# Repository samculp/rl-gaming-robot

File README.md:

# RL Gaming Robot

The RL Gaming Robot is a senior design project focused on developing a Reinforcement Learning system that learns to play games through repeated attempts and applies its learned behavior to a game to ultimately improve its score.

The current target game is Tetris. The long-term goal is for the RL agent to make gameplay decisions and output controller commands that are translated into physical actions pressed on a controller by a robotic system.

This repository contains the software and hardware elements used to create the project.

## Repository Structure

```text
RL-Gaming-Robot/

├── hardware/
│   ├── experiments/
│   │   ├── actuator_pulse/
│   │   └── cad_files/
│   └── production/
│
├── software/
│   ├── requirements/
│   ├── environment/
│   ├── agent/
│   └── test_cases/
│
└── README.md
```

## Hardware

The `hardware` directory contains the mechanical and electronic development files for the RL Gaming Robot.

This includes:

* Actuator experiments and testing
* CAD models and mechanical designs
* Controller mounting and interaction components
* Production hardware designs
* Hardware documentation and validation

See the [hardware README](hardware/README.md) for additional information.

## Software

The `software` directory contains the software required to develop and operate the RL system.

This includes:

* Python environment and dependency requirements
* Game environment code
* Reinforcement Learning agent code
* Software test cases

The software is responsible for interacting with the game environment, training and executing the RL agent, and producing controller actions for the hardware system.

See the [software README](software/README.md) for additional information.

## System Overview

The intended system operates as a feedback loop:

```text
┌─────────────────┐
│    NES Tetris   │
└────────┬────────┘
         │
         │ Game State
         ▼
┌─────────────────┐
│ Game Environment│
└────────┬────────┘
         │
         │ State
         ▼
┌─────────────────┐
│    RL Agent     │
└────────┬────────┘
         │
         │ Controller Action
         ▼
┌─────────────────┐
│ Robot Controller│
└────────┬────────┘
         │
         │ Physical Command
         ▼
┌─────────────────┐
│  Robotic System  │
└────────┬────────┘
         │
         │ Button Press
         ▼
┌─────────────────┐
│  NES Controller │
└────────┬────────┘
         │
         └──────────────► NES Tetris
```

The game produces a new state after each action, allowing the RL agent to continually evaluate the game and select its next action.

## Testing

Testing is an integral part of the project and is performed throughout both software and hardware development.

Software testing focuses on:

* Game-state processing
* RL agent behavior
* Action generation
* Software component integration
* Model performance and repeatability

Hardware testing focuses on:

* Actuator performance
* Button press accuracy
* Timing and reliability
* Mechanical positioning
* Hardware/software integration

Test cases are maintained within the appropriate software and hardware directories.

## Development Philosophy

The project is organized around **experimentation, validation, and integration**.

Development follows these general principles:

1. **Experiment** — Develop and test individual concepts and components.
2. **Validate** — Verify that components meet their intended requirements.
3. **Integrate** — Combine validated software and hardware components.
4. **Test** — Evaluate the complete system and identify integration issues.
5. **Iterate** — Use test results to improve the system.

Experimental implementations should be validated before being incorporated into the production system.

## Project Goals

The primary goals of the RL Gaming Robot project are to:

* Develop an RL agent capable of improving its gameplay through repeated attempts.
* Create a software environment for training and evaluating the agent.
* Develop a robotic system capable of physically interacting with a gaming controller.
* Establish reliable communication between the software and hardware systems.
* Test the performance and reliability of the complete system.
* Demonstrate the transfer of learned behavior from the software environment to physical gameplay.

## Current Development Status

The project is being developed incrementally, beginning with the software RL environment and agent before progressing toward full hardware integration.

Major development stages include:

1. Software environment development
2. RL agent development and training
3. Software testing and performance evaluation
4. Hardware development and validation
5. Software/hardware integration
6. Full-system testing
7. Final NES Tetris demonstration

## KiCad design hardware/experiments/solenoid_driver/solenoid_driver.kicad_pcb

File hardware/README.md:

# Hardware

Hardware design, firmware, schematics, experiments, and documentation for the RL gaming robot.

## Directories

* [`electronics/`](electronics/) — Electrical system documentation, PCB design, power budget, and wiring diagrams.
* [`mechanical/`](mechanical/) — Mechanical design documentation and CAD files.
* [`firmware/`](firmware/) — Arduino firmware for the hardware control system.
* [`experiments/`](experiments/) — Hardware and controller experiments used during development.
* [`photos/`](photos/) — Miscellaneous ardware photos.

## System Overview

For detailed electrical architecture and subsystem documentation, see [`electronics/`](electronics/).

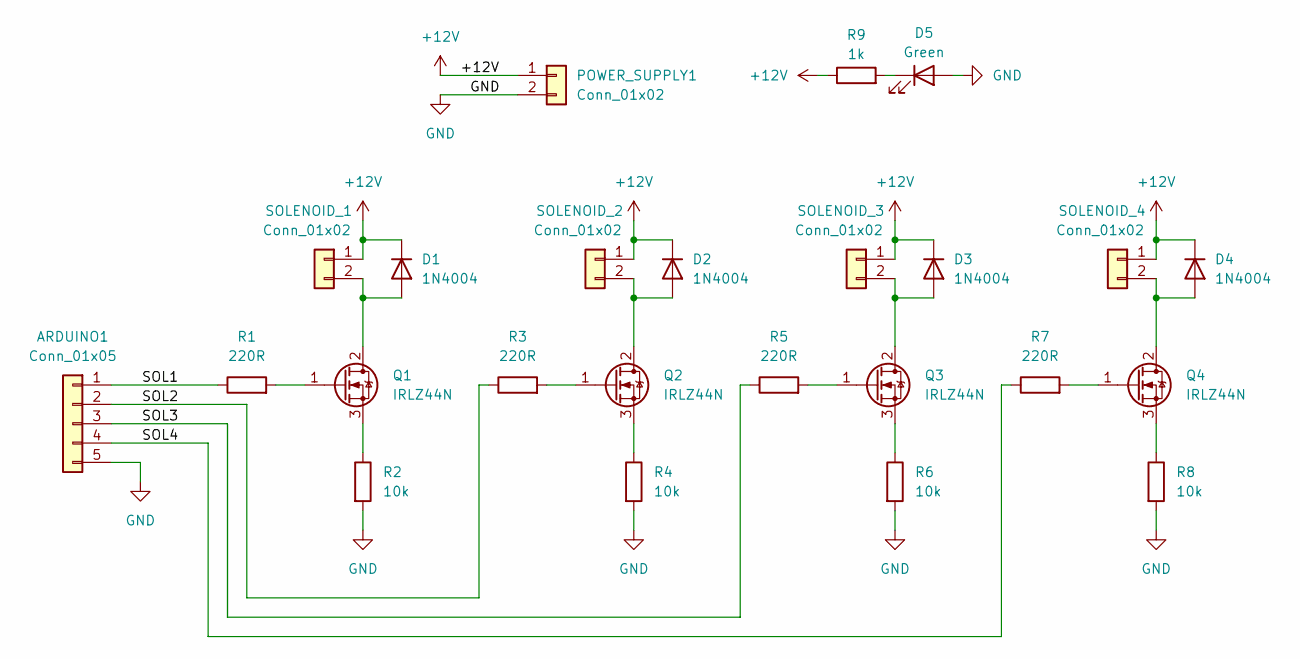
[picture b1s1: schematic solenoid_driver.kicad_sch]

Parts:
ARDUINO1: Conn_01x05; TerminalBlock_CUI_TB007-508-05_1x05_P5.08mm_Horizontal
D1, D2, D3, D4: 1N4004; D_DO-41_SOD81_P10.16mm_Horizontal
D5: Green; LED_D5.0mm
POWER_SUPPLY1: Conn_01x02; TerminalBlock_CUI_TB007-508-02_1x02_P5.08mm_Horizontal
Q1, Q2, Q3, Q4: IRLZ44N; TO-220-3_Vertical
R1, R3, R5, R7: 220R; R_Axial_DIN0207_L6.3mm_D2.5mm_P10.16mm_Horizontal
R2, R4, R6, R8: 10k; R_Axial_DIN0207_L6.3mm_D2.5mm_P10.16mm_Horizontal
R9: 1k; R_Axial_DIN0207_L6.3mm_D2.5mm_P10.16mm_Horizontal
SOLENOID_1, SOLENOID_2, SOLENOID_3, SOLENOID_4: Conn_01x02; TerminalBlock_CUI_TB007-508-02_1x02_P5.08mm_Horizontal

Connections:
+12V: D1.1 (K), D2.1 (K), D3.1 (K), D4.1 (K), POWER_SUPPLY1.1, R9.1, SOLENOID_1.1, SOLENOID_2.1, SOLENOID_3.1, SOLENOID_4.1
/SOL1: ARDUINO1.1, R1.1
/SOL2: ARDUINO1.2, R3.1
/SOL3: ARDUINO1.3, R5.1
/SOL4: ARDUINO1.4, R7.1
GND: ARDUINO1.5, D5.2 (A), POWER_SUPPLY1.2, R2.2, R4.2, R6.2, R8.2
unnamed: D1.2 (A), Q1.2 (D), SOLENOID_1.2
unnamed: D2.2 (A), Q2.2 (D), SOLENOID_2.2
unnamed: D3.2 (A), Q3.2 (D), SOLENOID_3.2
unnamed: D4.2 (A), Q4.2 (D), SOLENOID_4.2
unnamed: D5.1 (K), R9.2
unnamed: Q1.1 (G), R1.2
unnamed: Q1.3 (S), R2.1
unnamed: Q2.1 (G), R3.2
unnamed: Q2.3 (S), R4.1
unnamed: Q3.1 (G), R5.2
unnamed: Q3.3 (S), R6.1
unnamed: Q4.1 (G), R7.2
unnamed: Q4.3 (S), R8.1

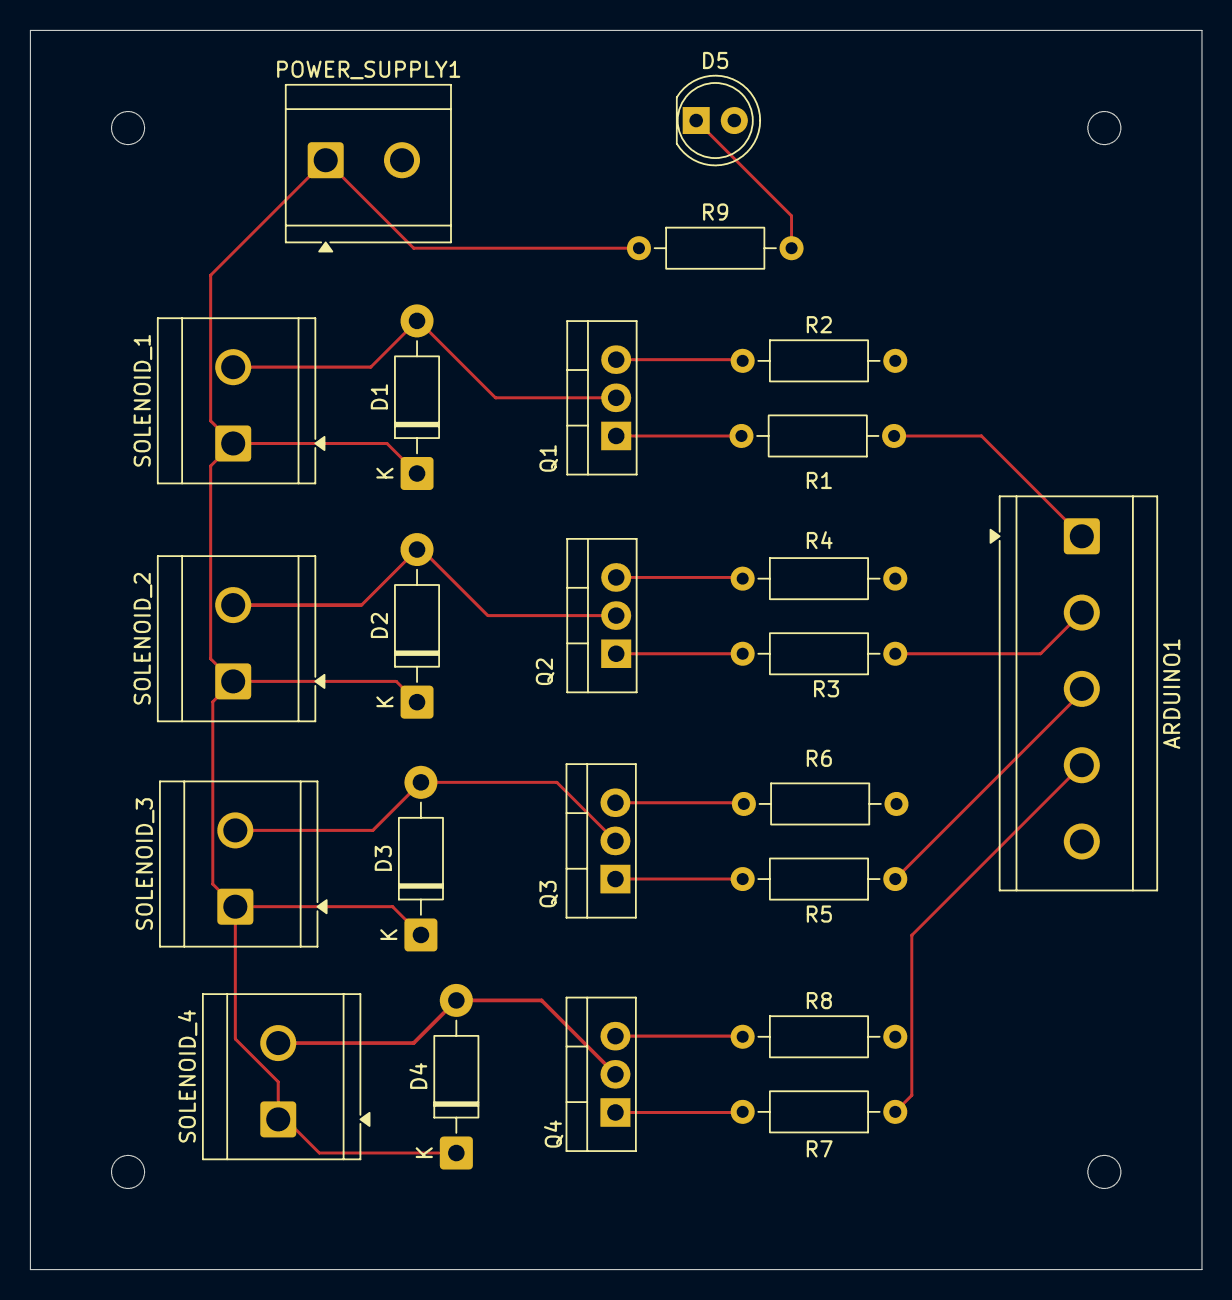
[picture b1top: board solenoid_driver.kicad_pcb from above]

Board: 2 copper layers, 78.0 x 82.5 mm, 24 parts (0 on the bottom side), 19 nets.

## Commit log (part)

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2026-04-10 initial servo plunger test
2026-04-10 increase time between presses
2026-04-15 servo test and cradle STL file
